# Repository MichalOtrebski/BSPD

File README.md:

# BSPD
A safety device which detects hard braking and acceleration and shuts the engine down.

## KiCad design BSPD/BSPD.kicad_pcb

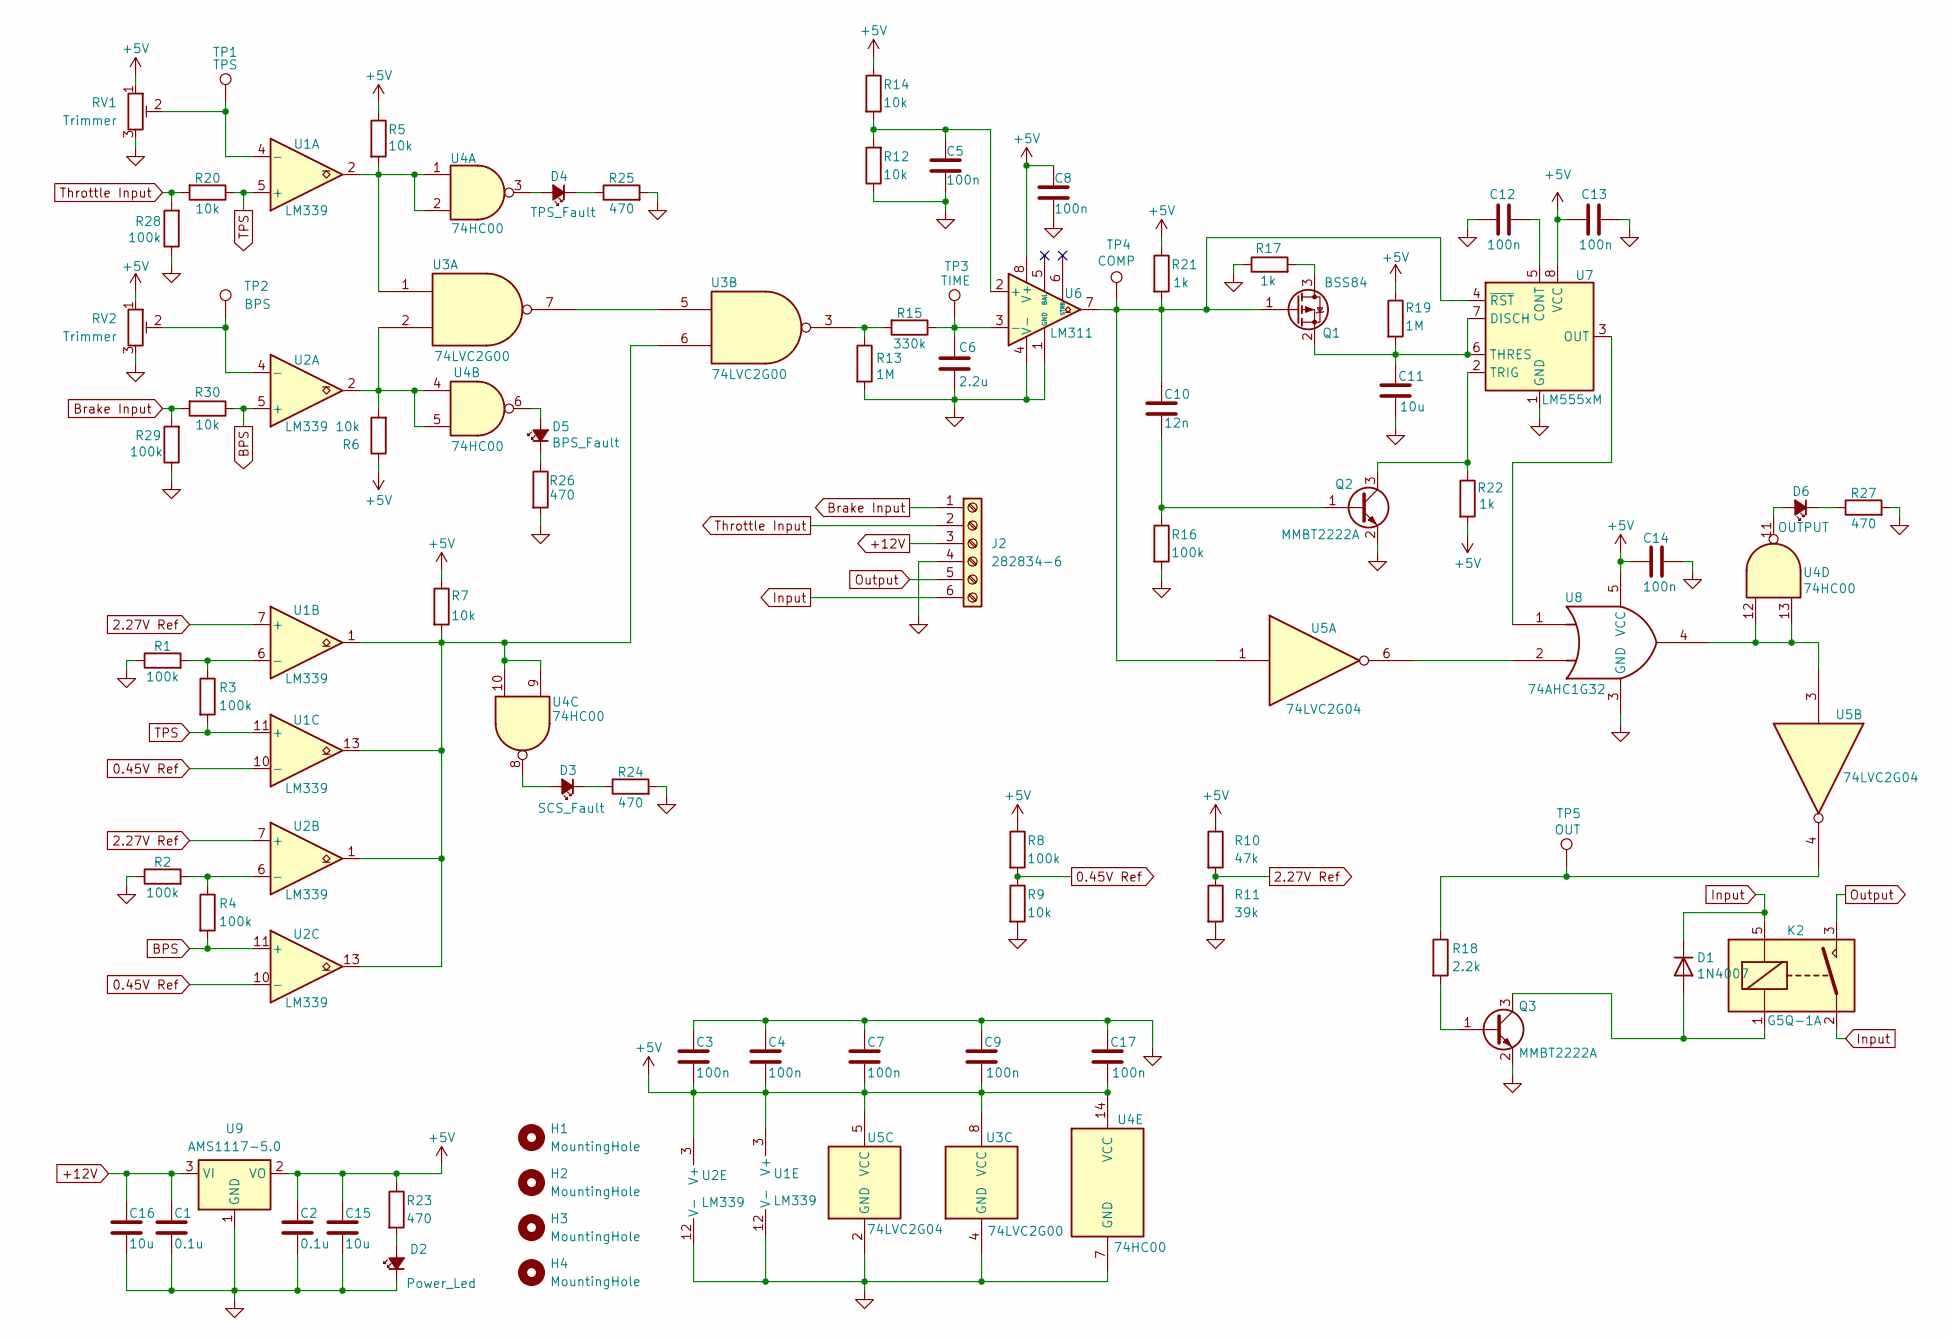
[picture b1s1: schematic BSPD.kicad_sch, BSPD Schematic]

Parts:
C1, C2: 0.1u; C_0402_1005Metric
C3, C4, C5, C7, C8, C9, C12, C13, C14, C17: 100n; C_0402_1005Metric
C6: 2.2u; C_0805_2012Metric
C10: 12n; C_0805_2012Metric
C11: 10u; C_0805_2012Metric
C15, C16: 10u; C_0402_1005Metric
D1: 1N4007; D_SMA
D2: Power_Led; LED_0603_1608Metric
D3: SCS_Fault; LED_0603_1608Metric
D4: TPS_Fault; LED_0603_1608Metric
D5: BPS_Fault; LED_0603_1608Metric
D6: OUTPUT; LED_0603_1608Metric
H1, H2, H3, H4: MountingHole; MountingHole_2.2mm_M2_Pad
J2: 282834-6; TerminalBlock_TE_282834-6_1x06_P2.54mm_Horizontal
K2: G5Q-1A; Relay_SPST_Omron-G5Q-1A
Q1: BSS84; SOT-23
Q2, Q3: MMBT2222A; SOT-23
R1, R2, R3, R4, R8, R16, R28, R29: 100k; R_0603_1608Metric
R5, R6, R7, R9, R12, R14, R20, R30: 10k; R_0603_1608Metric
R10: 47k; R_0603_1608Metric
R11: 39k; R_0603_1608Metric
R13, R19: 1M; R_0603_1608Metric
R15: 330k; R_0603_1608Metric
R17, R21, R22: 1k; R_0603_1608Metric
R18: 2.2k; R_0603_1608Metric
R23, R24, R25, R26, R27: 470; R_0603_1608Metric
RV1, RV2: Trimmer; Potentiometer_Bourns_3314J_Vertical
TP1: TPS; TestPoint_Pad_D1.5mm
TP2: BPS; TestPoint_Pad_D1.5mm
TP3: TIME; TestPoint_Pad_D1.5mm
TP4: COMP; TestPoint_Pad_D1.5mm
TP5: OUT; TestPoint_Pad_D1.5mm
U1, U2: LM339; SOIC127P600X175-14N
U3: 74LVC2G00; SOP50P310X90-8N
U4: 74HC00; SOIC127P600X175-14N
U5: 74LVC2G04; SOT-23-6
U6: LM311; SOIC-8_3.9x4.9mm_P1.27mm
U7: LM555xM; SOIC-8_3.9x4.9mm_P1.27mm
U8: 74AHC1G32; SOT-23-5
U9: AMS1117-5.0; SOT-223-3_TabPin2

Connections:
0.45V Ref: R8.2, R9.1, U1.10 (-), U2.10 (-)
2.27V Ref: R10.2, R11.1, U1.7 (+), U2.7 (+)
+5V: C2.1, C3.2, C4.2, C7.2, C8.1, C9.2, C13.1, C14.2, C15.1, C17.2, R5.1, R6.1, R7.1, R8.1, R10.1, R14.1, R19.1, R21.1, R22.2, R23.1, RV1.1, RV2.1, U1.3 (V+), U2.3 (V+), U3.8 (VCC), U4.14 (VCC), U5.5 (VCC), U6.8 (V+), U7.8 (VCC), U8.5 (VCC), U9.2 (VO)
+12V: C1.1, C16.1, J2.3, U9.3 (VI)
BPS: R4.2, R30.1, U2.5 (+), U2.11 (+)
Brake Input: J2.1, R29.2, R30.2
GND: C1.2, C2.2, C3.1, C4.1, C5.2, C6.2, C7.1, C8.2, C9.1, C11.2, C12.1, C13.2, C14.1, C15.2, C16.2, C17.1, D2.1 (K), J2.4, Q2.2 (E), Q3.2 (E), R1.1, R2.1, R9.2, R11.2, R12.1, R13.2, R16.2, R17.1, R24.2, R25.2, R26.2, R27.2, R28.1, R29.1, RV1.3, RV2.3, U1.12 (V-), U2.12 (V-), U3.4 (GND), U4.7 (GND), U5.2 (GND), U6.1 (GND), U6.4 (V-), U7.1 (GND), U8.3 (GND), U9.1 (GND)
Input: D1.1 (K), J2.6, K2.2, K2.5
unnamed: D1.2 (A), K2.1, Q3.3 (C)
unnamed: D2.2 (A), R23.2
unnamed: D3.2 (A), U4.8
unnamed: D3.1 (K), R24.1
unnamed: D4.2 (A), U4.3
unnamed: D4.1 (K), R25.1
unnamed: D5.2 (A), U4.6
unnamed: D5.1 (K), R26.1
unnamed: D6.2 (A), U4.11
unnamed: D6.1 (K), R27.1
unnamed: Q1.3 (D), R17.2
unnamed: C10.1, Q1.1 (G), R21.2, TP4.1, U5.1, U6.7, U7.4 (~RST)
unnamed: C11.1, Q1.2 (S), R19.2, U7.6 (THRES), U7.7 (DISCH)
unnamed: C10.2, Q2.1 (B), R16.1
unnamed: Q2.3 (C), R22.1, U7.2 (TRIG)
unnamed: Q3.1 (B), R18.2
unnamed: R5.2, U1.2, U3.1, U4.1, U4.2
unnamed: R6.2, U2.2, U3.2, U4.4, U4.5
unnamed: R7.2, U1.1, U1.13, U2.1, U2.13, U3.6, U4.9, U4.10
unnamed: R13.1, R15.2, U3.3
unnamed: R18.1, TP5.1, U5.4
unnamed: RV1.2, TP1.1, U1.4 (-)
unnamed: R1.2, R3.1, U1.6 (-)
unnamed: RV2.2, TP2.1, U2.4 (-)
unnamed: R2.2, R4.1, U2.6 (-)
unnamed: U3.5, U3.7
unnamed: U4.12, U4.13, U5.3, U8.4
unnamed: U5.6, U8.2
unnamed: C5.1, R12.2, R14.2, U6.2 (+)
unnamed: C6.1, R15.1, TP3.1, U6.3 (-)
unnamed: C12.2, U7.5 (CONT)
unnamed: U7.3 (OUT), U8.1
Output: J2.5, K2.3
TPS: R3.2, R20.1, U1.5 (+), U1.11 (+)
Throttle Input: J2.2, R20.2, R28.2

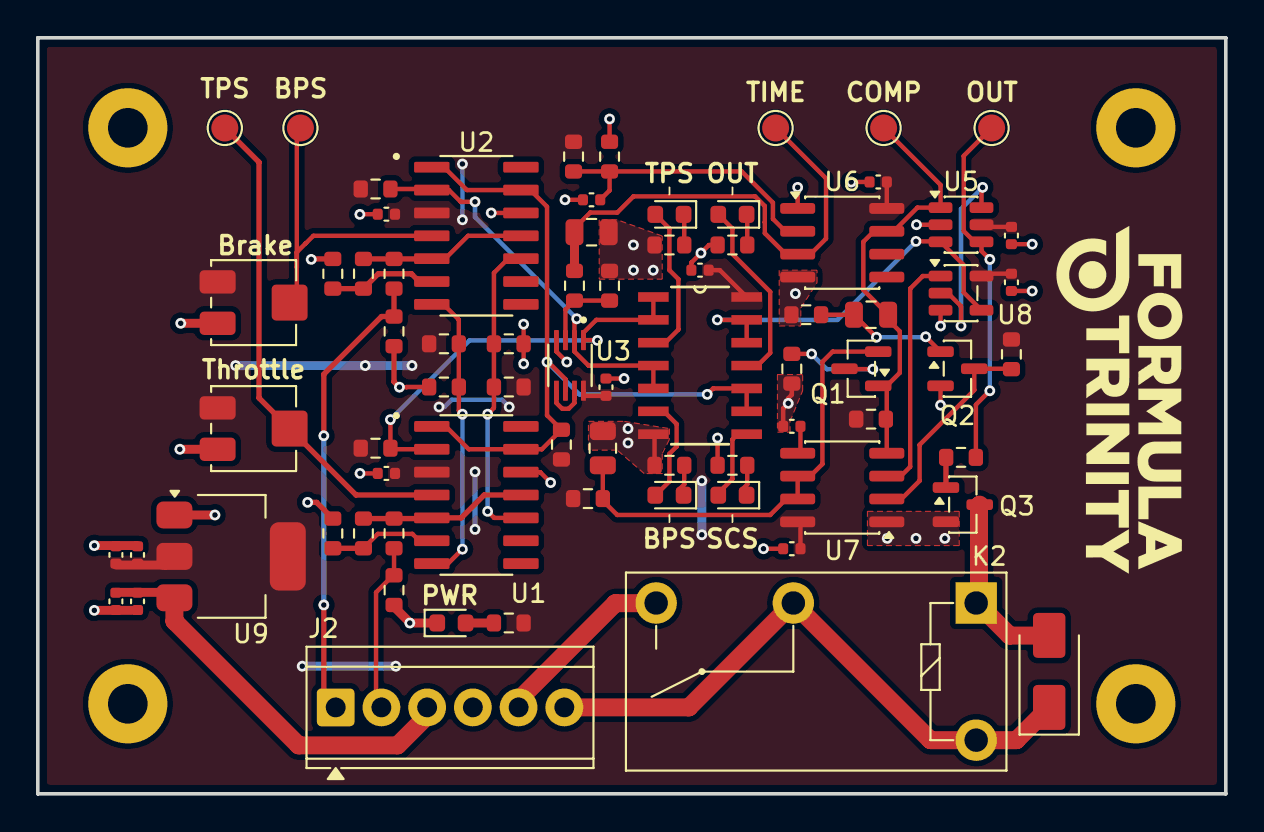
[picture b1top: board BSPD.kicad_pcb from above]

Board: 2 copper layers, 66.0 x 42.0 mm, 78 parts (0 on the bottom side), 43 nets.

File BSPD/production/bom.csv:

Designator,Footprint,Quantity,Value,LCSC Part #
"C1, C2",0402,2,0.1u,
C10,0805,1,12n,
C11,0805,1,10u,
"C12, C13, C14, C17, C3, C4, C5, C7, C8, C9",0402,10,100n,
"C15, C16",0402,2,10u,
C6,0805,1,2.2u,
D1,D_SMA,1,1N4007,
D2,0603,1,Power_Led,
D3,0603,1,SCS_Fault,
D4,0603,1,TPS_Fault,
D5,0603,1,BPS_Fault,
D6,0603,1,OUTPUT,
J2,TerminalBlock_TE_282834-6_1x06_P2.54mm_Horizontal,1,282834-6,
K2,Relay_SPST_Omron-G5Q-1A,1,G5Q-1A,
Q1,SOT-23,1,BSS84,
"Q2, Q3",SOT-23,2,MMBT2222A,
"R1, R16, R2, R28, R29, R3, R4, R8",0603,8,100k,
R10,0603,1,47k,
R11,0603,1,39k,
"R12, R14, R20, R30, R5, R6, R7, R9",0603,8,10k,
"R13, R19",0603,2,1M,
R15,0603,1,330k,
"R17, R21, R22",0603,3,1k,
R18,0603,1,2.2k,
"R23, R24, R25, R26, R27",0603,5,220,
"RV1, RV2",Potentiometer_Bourns_3314J_Vertical,2,Trimmer,
TP1,TestPoint_Pad_D1.5mm,1,TPS,
TP2,TestPoint_Pad_D1.5mm,1,BPS,
TP3,TestPoint_Pad_D1.5mm,1,TIME,
TP4,TestPoint_Pad_D1.5mm,1,COMP,
TP5,TestPoint_Pad_D1.5mm,1,OUT,
"U1, U2",SOIC127P600X175-14N,2,LM339,
U3,SOP50P310X90-8N,1,74LVC2G00,
U4,SOIC127P600X175-14N,1,74HC00,
U5,SOT-23-6,1,74LVC2G04,
U6,SOIC-8_3.9x4.9mm_P1.27mm,1,LM311,
U7,SOIC-8_3.9x4.9mm_P1.27mm,1,LM555xM,
U8,SOT-23-5,1,74AHC1G32,
U9,SOT-223-3_TabPin2,1,AMS1117-5.0,

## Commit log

2026-04-07 v0.1
    Majority of the schematic and PCB uplaoded, somr parts need editing, primarily extra debugging leds, and inverting the trimmer and sensor inputs.
2026-04-07 v0.2
    updated design, fixed trimmers, added extra debug LEDs.
2026-04-08 v0.3
    minor silscreen changes
2026-04-08 minor resistor changes and symbol correction
2026-04-13 minor changes
2026-04-13 v0.4
2026-04-28 v1.0
    1.0 release, designed and purchased for FTX7 in 2026
